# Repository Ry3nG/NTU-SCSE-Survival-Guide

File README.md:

# NTU-SCSE-Survival-Guide
Hi there, I'm glad you found this repository.

I created this repository because one day I was organizing my hard drive and found a lot of code and assignments from my freshman year. I thought it would be a good idea to share it with juniors. I hope this repository will help you in your journey in NTU SCSE. Spread the word and share this repository with your friends.

:sparkles:Please feel free to contribute to this repository and make it better. If you have any questions, feel free to open an issue:sparkles:

:pushpin:Note: This repository is still under construction. I will be adding more content as time goes by. If you have any suggestions, feel free to open an issue.:pushpin:

:no_entry_sign:Disclaimer: I do not guarantee that all the works in this repository is correct. Also, NTU does not endorse this repository. I am not responsible for any consequences that may arise from using this repository. Please remember that no plagiarism is allowed in NTU. Please do not copy and paste the code from this repository. I am not responsible for any consequences that may arise from using this repository. Please use this repository at your own risk. :no_entry_sign:

## What to expect :heavy_plus_sign:

- [x] :books: Study notes
- [x] :page_with_curl: Lab assignments
- [x] :computer: Project assignments 
- [x] :pencil: [Past year exam papers](https://entuedu-my.sharepoint.com/personal/scse-academics_e_ntu_edu_sg/_layouts/15/onedrive.aspx?id=%2Fpersonal%2Fscse%2Dacademics%5Fe%5Fntu%5Fedu%5Fsg%2FDocuments%2FSCSE%20Past%20Year%20Papers&ga=1)

## Directory Structure :file_folder:
* Year 1 Modules
  * [SC1003](https://github.com/Ry3nG/NTU-SCSE-Survival-Guide/blob/63125223ba3fbce1692d6bb430d10afd18555996/Year1/SC1003) - Introduction to Computational Thinking & Programming 
  * [SC1007](https://github.com/Ry3nG/NTU-SCSE-Survival-Guide/blob/63125223ba3fbce1692d6bb430d10afd18555996/Year1/SC1007) - Data Structures & Algorithms 
  * [SC1015](https://github.com/Ry3nG/NTU-SCSE-Survival-Guide/blob/e838eea947de3046945bb1c5bfa82d6b12342de5/Year1/SC1015) - Data Science and Artificial Intelligence
* Year 2 Modules
  * [SC2002](https://github.com/Ry3nG/NTU-SCSE-Survival-Guide/blob/1c191aafbaf08b72edd439501faf1cfb49756c34/Year2/SC2002) - Object Oriented Design & Programming
  * [SC2001](https://github.com/Ry3nG/NTU-SCSE-Survival-Guide/blob/main/Year2/SC2001) - Algorithms Design & Analysis
  * [SC2104](https://github.com/Ry3nG/NTU-SCSE-Survival-Guide/blob/main/Year2/SC2104) - Sensors, Interfacing & Digital Control
  * [SC2107](https://github.com/Ry3nG/NTU-SCSE-Survival-Guide/blob/main/Year2/SC2107) - Microprocessor System Design and Development
  * [SC2103](https://github.com/Ry3nG/NTU-SCSE-Survival-Guide/tree/main/Year2/SC2103) - Digital System Design
  * [SC2005](https://github.com/Ry3nG/NTU-SCSE-Survival-Guide/tree/main/Year2/SC2005) - Operating Systems
  * [SC2008](https://github.com/Ry3nG/NTU-SCSE-Survival-Guide/tree/main/Year2/SC2008) - Computer Networks
* SC2079 - Multi-Disciplinary Design Project
  * I was responsible for the STM and hardware part for the MDP project, the related files can be found [here](https://github.com/Ry3nG/STM32-Robot-Hardware-Control)
* Year 3 Modules
  * [SC3102](https://github.com/Ry3nG/NTU-SCSE-Survival-Guide/tree/year3-mods/Year3/SC3102) - Signals, Systems, and Transforms
  * [SC3103](https://github.com/Ry3nG/NTU-SCSE-Survival-Guide/tree/year3-mods/Year3/SC3103) - Embedded Programming
  * [SC3050](https://github.com/Ry3nG/NTU-SCSE-Survival-Guide/tree/year3-mods/Year3/SC3050) - Advanced Computer Architecture
## What you won't find in this repository :heavy_minus_sign:
Your exam answers, obviously. :sweat_smile:
Also, this repository is not a replacement for your own effort. You should still study hard and do your own research. This repository is providing you with some resources that you can refer to when you struggles.

## Contribute
You have useful information that is missing in here? 
Feel free to contribute to this project and help more future NTU students :sparkles:

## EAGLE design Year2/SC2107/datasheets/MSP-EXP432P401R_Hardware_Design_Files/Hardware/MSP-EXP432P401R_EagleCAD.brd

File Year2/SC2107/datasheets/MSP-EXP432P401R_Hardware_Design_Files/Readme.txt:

MSP-EXP432P401R Hardware Design Files v3.00.00
Texas Instruments, Inc.

********************************************************************************
Welcome to the MSP-EXP432P401R LaunchPad!
********************************************************************************

In this package, you will find hardware design files that can help you quickly
get started on developing your own project.

Available in the 'Hardware' folder are the complete board schematic and layout,
bill of material and Gerber files.

You can also find various web links in the 'Documentation' folder pointing to
the LaunchPad's Homepage, Quick Start Guide, User's Guide, and Software Examples.

For more resources, be sure to visit www.ti.com/tool/msp-exp432p401r

********************************************************************************
Revision History
********************************************************************************
Ver 3.00.00 - June 3rd, 2016
- New Rev2.0 PCB hardware design
- Added BOOSTXL-BATPAKMKII and BOOSTXL-SENSORS demos

Ver 2.10.00 - February 17th, 2016
- Header file, Driver Library updates

Ver 2.00.00 - November 4th, 2015
- Updated demo projects for CMSIS header file updates
- Added CapTouch BoosterPack demos

Ver 1.05.00 - November 4th, 2015
- Bug fixes to demo projects

Ver 1.04.00 - August 24th, 2015
- Fixed Educational Boosterpack MKII example projectSpec include path error in Linux

Ver 1.03.00 - June 22nd, 2015
- Added MacOSX + Linux support for OOB GUI and DSLite
- Added Educational Boosterpack MKII example projects

Ver 1.02.00 - May 15th, 2015
- Added link to Software Examples download

Ver 1.01.02 - April 14th, 2015
- Bug fixes for OutOfBox demo
- Added KEIL project files to software examples
- Updated IAR project files
- Added Blink LED example

Ver 1.00.05 - March 24th, 2015
- Initial Release

********************************************************************************
Project File Listing
********************************************************************************
|--Documentation                      : Folder containing links to more resources
|--Hardware                           : Folder containing hardware design files,
                                        bill of material and gerber files
|--Readme.txt                         : This file

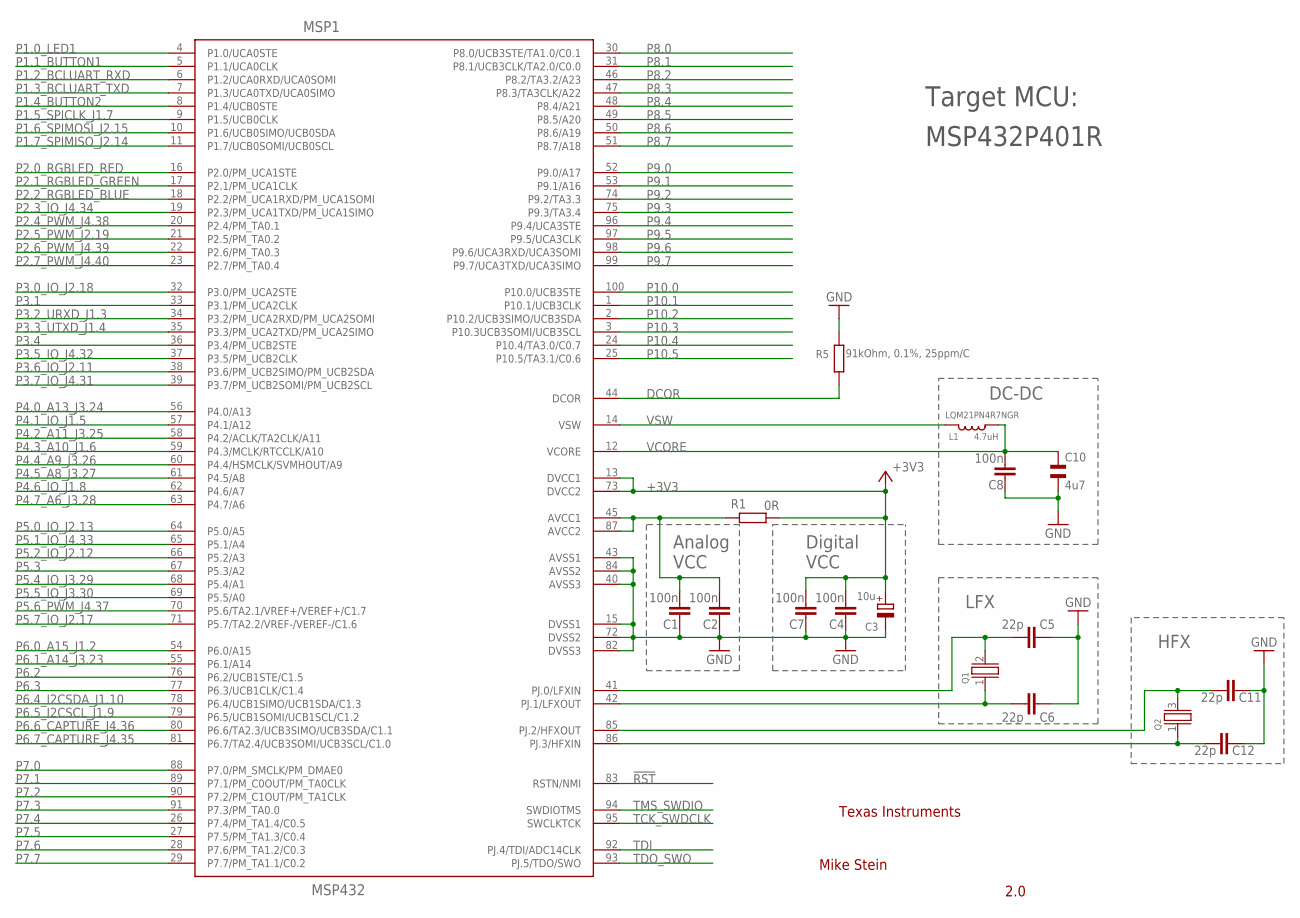
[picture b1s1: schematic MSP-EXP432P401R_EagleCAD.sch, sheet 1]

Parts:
C1, C2, C4, C7, C8: 100n; 0402
C3: 10u; A/3216-18R
C5, C6, C11, C12: 22p; 0402
C10: 4u7; CSMD0805
L1: 4.7uH; 0806
MSP1: MSP432; PZ100
Q1: CRYSTALLF_GENERAL; LF_XTAL
Q2: CRYSTALEPSON_FA-238; FA-238
R1: 0R; 0402
R5: 91kOhm, 0.1%, 25ppm/C; 0805

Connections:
!RST: MSP1.83 (RSTN/NMI); also elsewhere on the board
+3V3: C3.+, C4.1, C7.1, MSP1.13 (DVCC1), MSP1.73 (DVCC2), R1.1; also elsewhere on the board
DCOR: MSP1.44 (DCOR), R5.1
unnamed: C1.1, C2.1, MSP1.45 (AVCC1), MSP1.87 (AVCC2), R1.2
unnamed: C6.1, MSP1.42 (PJ.1/LFXOUT), Q1.1
unnamed: C5.1, MSP1.41 (PJ.0/LFXIN), Q1.2
P1.0_LED1: MSP1.4 (P1.0/UCA0STE); also elsewhere on the board
P1.1_BUTTON1: MSP1.5 (P1.1/UCA0CLK); also elsewhere on the board
P1.2_BCLUART_RXD: MSP1.6 (P1.2/UCA0RXD/UCA0SOMI); also elsewhere on the board
P1.3_BCLUART_TXD: MSP1.7 (P1.3/UCA0TXD/UCA0SIMO); also elsewhere on the board
P1.4_BUTTON2: MSP1.8 (P1.4/UCB0STE); also elsewhere on the board
P1.5_SPICLK_J1.7: MSP1.9 (P1.5/UCB0CLK); also elsewhere on the board
P1.6_SPIMOSI_J2.15: MSP1.10 (P1.6/UCB0SIMO/UCB0SDA); also elsewhere on the board
P1.7_SPIMISO_J2.14: MSP1.11 (P1.7/UCB0SOMI/UCB0SCL); also elsewhere on the board
P2.0_RGBLED_RED: MSP1.16 (P2.0/PM_UCA1STE); also elsewhere on the board
P2.1_RGBLED_GREEN: MSP1.17 (P2.1/PM_UCA1CLK); also elsewhere on the board
P2.2_RGBLED_BLUE: MSP1.18 (P2.2/PM_UCA1RXD/PM_UCA1SOMI); also elsewhere on the board
P2.3_IO_J4.34: MSP1.19 (P2.3/PM_UCA1TXD/PM_UCA1SIMO); also elsewhere on the board
P2.4_PWM_J4.38: MSP1.20 (P2.4/PM_TA0.1); also elsewhere on the board
P2.5_PWM_J2.19: MSP1.21 (P2.5/PM_TA0.2); also elsewhere on the board
P2.6_PWM_J4.39: MSP1.22 (P2.6/PM_TA0.3); also elsewhere on the board
P2.7_PWM_J4.40: MSP1.23 (P2.7/PM_TA0.4); also elsewhere on the board
P3.0_IO_J2.18: MSP1.32 (P3.0/PM_UCA2STE); also elsewhere on the board
P3.1: MSP1.33 (P3.1/PM_UCA2CLK)
P3.2_URXD_J1.3: MSP1.34 (P3.2/PM_UCA2RXD/PM_UCA2SOMI); also elsewhere on the board
P3.3_UTXD_J1.4: MSP1.35 (P3.3/PM_UCA2TXD/PM_UCA2SIMO); also elsewhere on the board
P3.4: MSP1.36 (P3.4/PM_UCB2STE)
P3.5_IO_J4.32: MSP1.37 (P3.5/PM_UCB2CLK); also elsewhere on the board
P3.6_IO_J2.11: MSP1.38 (P3.6/PM_UCB2SIMO/PM_UCB2SDA); also elsewhere on the board
P3.7_IO_J4.31: MSP1.39 (P3.7/PM_UCB2SOMI/PM_UCB2SCL); also elsewhere on the board
P4.0_A13_J3.24: MSP1.56 (P4.0/A13); also elsewhere on the board
P4.1_IO_J1.5: MSP1.57 (P4.1/A12); also elsewhere on the board
P4.2_A11_J3.25: MSP1.58 (P4.2/ACLK/TA2CLK/A11); also elsewhere on the board
P4.3_A10_J1.6: MSP1.59 (P4.3/MCLK/RTCCLK/A10); also elsewhere on the board
P4.4_A9_J3.26: MSP1.60 (P4.4/HSMCLK/SVMHOUT/A9); also elsewhere on the board
P4.5_A8_J3.27: MSP1.61 (P4.5/A8); also elsewhere on the board
P4.6_IO_J1.8: MSP1.62 (P4.6/A7); also elsewhere on the board
P4.7_A6_J3.28: MSP1.63 (P4.7/A6); also elsewhere on the board
P5.0_IO_J2.13: MSP1.64 (P5.0/A5); also elsewhere on the board
P5.1_IO_J4.33: MSP1.65 (P5.1/A4); also elsewhere on the board
P5.2/XT2IN: C12.1, MSP1.86 (PJ.3/HFXIN), Q2.1
P5.2_IO_J2.12: MSP1.66 (P5.2/A3); also elsewhere on the board
P5.3: MSP1.67 (P5.3/A2); also elsewhere on the board
P5.3/XT2OUT: C11.1, MSP1.85 (PJ.2/HFXOUT), Q2.3 (2)
P5.4_IO_J3.29: MSP1.68 (P5.4/A1); also elsewhere on the board
P5.5_IO_J3.30: MSP1.69 (P5.5/A0); also elsewhere on the board
P5.6_PWM_J4.37: MSP1.70 (P5.6/TA2.1/VREF+/VEREF+/C1.7); also elsewhere on the board
P5.7_IO_J2.17: MSP1.71 (P5.7/TA2.2/VREF-/VEREF-/C1.6); also elsewhere on the board
P6.0_A15_J1.2: MSP1.54 (P6.0/A15); also elsewhere on the board
P6.1_A14_J3.23: MSP1.55 (P6.1/A14); also elsewhere on the board
P6.2: MSP1.76 (P6.2/UCB1STE/C1.5); also elsewhere on the board
P6.3: MSP1.77 (P6.3/UCB1CLK/C1.4); also elsewhere on the board
P6.4_I2CSDA_J1.10: MSP1.78 (P6.4/UCB1SIMO/UCB1SDA/C1.3); also elsewhere on the board
P6.5_I2CSCL_J1.9: MSP1.79 (P6.5/UCB1SOMI/UCB1SCL/C1.2); also elsewhere on the board
P6.6_CAPTURE_J4.36: MSP1.80 (P6.6/TA2.3/UCB3SIMO/UCB3SDA/C1.1); also elsewhere on the board
P6.7_CAPTURE_J4.35: MSP1.81 (P6.7/TA2.4/UCB3SOMI/UCB3SCL/C1.0); also elsewhere on the board
P7.0: MSP1.88 (P7.0/PM_SMCLK/PM_DMAE0); also elsewhere on the board
P7.1: MSP1.89 (P7.1/PM_C0OUT/PM_TA0CLK); also elsewhere on the board
P7.2: MSP1.90 (P7.2/PM_C1OUT/PM_TA1CLK); also elsewhere on the board
P7.3: MSP1.91 (P7.3/PM_TA0.0); also elsewhere on the board
P7.4: MSP1.26 (P7.4/PM_TA1.4/C0.5); also elsewhere on the board
P7.5: MSP1.27 (P7.5/PM_TA1.3/C0.4); also elsewhere on the board
P7.6: MSP1.28 (P7.6/PM_TA1.2/C0.3); also elsewhere on the board
P7.7: MSP1.29 (P7.7/PM_TA1.1/C0.2); also elsewhere on the board
P8.0: MSP1.30 (P8.0/UCB3STE/TA1.0/C0.1); also elsewhere on the board
P8.1: MSP1.31 (P8.1/UCB3CLK/TA2.0/C0.0)
P8.2: MSP1.46 (P8.2/TA3.2/A23); also elsewhere on the board
P8.3: MSP1.47 (P8.3/TA3CLK/A22); also elsewhere on the board
P8.4: MSP1.48 (P8.4/A21); also elsewhere on the board
P8.5: MSP1.49 (P8.5/A20); also elsewhere on the board
P8.6: MSP1.50 (P8.6/A19); also elsewhere on the board
P8.7: MSP1.51 (P8.7/A18); also elsewhere on the board
P9.0: MSP1.52 (P9.0/A17); also elsewhere on the board
P9.1: MSP1.53 (P9.1/A16); also elsewhere on the board
P9.2: MSP1.74 (P9.2/TA3.3); also elsewhere on the board
P9.3: MSP1.75 (P9.3/TA3.4); also elsewhere on the board
P9.4: MSP1.96 (P9.4/UCA3STE); also elsewhere on the board
P9.5: MSP1.97 (P9.5/UCA3CLK); also elsewhere on the board
P9.6: MSP1.98 (P9.6/UCA3RXD/UCA3SOMI); also elsewhere on the board
P9.7: MSP1.99 (P9.7/UCA3TXD/UCA3SIMO); also elsewhere on the board
P10.0: MSP1.100 (P10.0/UCB3STE); also elsewhere on the board
P10.1: MSP1.1 (P10.1/UCB3CLK); also elsewhere on the board
P10.2: MSP1.2 (P10.2/UCB3SIMO/UCB3SDA); also elsewhere on the board
P10.3: MSP1.3 (P10.3UCB3SOMI/UCB3SCL); also elsewhere on the board
P10.4: MSP1.24 (P10.4/TA3.0/C0.7); also elsewhere on the board
P10.5: MSP1.25 (P10.5/TA3.1/C0.6); also elsewhere on the board
TCK_SWDCLK: MSP1.95 (SWCLKTCK); also elsewhere on the board
TDI: MSP1.92 (PJ.4/TDI/ADC14CLK); also elsewhere on the board
TDO_SWO: MSP1.93 (PJ.5/TDO/SWO); also elsewhere on the board
TMS_SWDIO: MSP1.94 (SWDIOTMS); also elsewhere on the board
VCORE: C8.1, C10.1, L1.1, MSP1.12 (VCORE)
VSW: L1.2, MSP1.14 (VSW)
XDS-GND: C1.2, C2.2, C3.-, C4.2, C5.2, C6.2, C7.2, C8.2, C10.2, C11.2, C12.2, MSP1.15 (DVSS1), MSP1.40 (AVSS3), MSP1.43 (AVSS1), MSP1.72 (DVSS2), MSP1.82 (DVSS3), MSP1.84 (AVSS2), R5.2; also elsewhere on the board

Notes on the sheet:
Target MCU:
Texas Instruments
LQM21PN4R7NGR
HFX
LFX
Analog
VCC
Digital
DC-DC
MSP432P401R

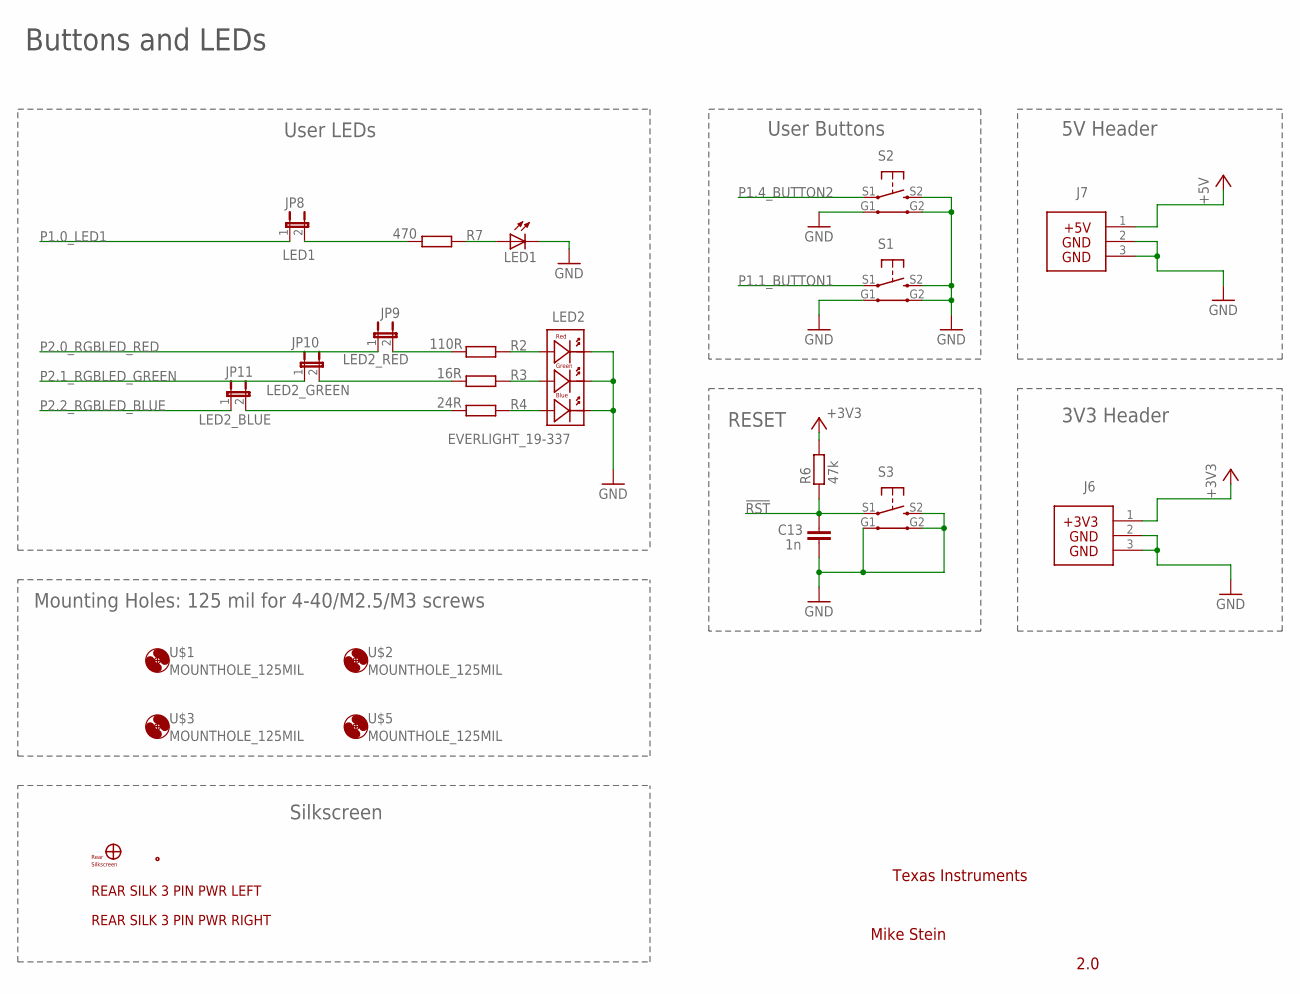
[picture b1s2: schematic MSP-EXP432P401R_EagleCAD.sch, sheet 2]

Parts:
C13: 1n; 0402
J6: HEADER 1X03; 3PIN_PWR_3V3
J7: BP_HEADERS_PWR_5V; 3PIN_PWR_5V
JP8: LED1; JP1M
JP9: LED2_RED; JP1M
JP10: LED2_GREEN; JP1M
JP11: LED2_BLUE; JP1M
LED1: LEDCHIPLED_0603; CHIPLED_0603
LED2: EVERLIGHT_19-337; RGB_LED
R2: 110R; 0402
R3: 16R; 0402
R4: 24R; 0402
R6: 47k; 0402
R7: 470; 0402
S1, S2, S3: TS-1188E
U$1, U$2, U$3, U$5: MOUNTHOLE_125MIL
U$6: SILK_HEADER_LABEL
U$7: MIKE_TM
U$8: P401R_REARSILK_REV2_0
U$9: BP_3PIN_SILK; 3PIN_PWR_SILK
U$10: BP_3PIN_SILK_RT; 3PIN_PWR_SILK_RT

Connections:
!RST: C13.1, R6.1, S3.S1; also elsewhere on the board
+3V3: J6.1, R6.2; also elsewhere on the board
+5V: J7.1; also elsewhere on the board
unnamed: JP9.2, R2.1
unnamed: LED2.5 (RA), R2.2
unnamed: LED2.6 (GA), R3.2
unnamed: LED2.4 (BA), R4.2
unnamed: LED1.A, R7.2
unnamed: JP10.2, R3.1
unnamed: JP11.2, R4.1
unnamed: JP8.2, R7.1
P1.0_LED1: JP8.1; also elsewhere on the board
P1.1_BUTTON1: S1.S1; also elsewhere on the board
P1.4_BUTTON2: S2.S1; also elsewhere on the board
P2.0_RGBLED_RED: JP9.1; also elsewhere on the board
P2.1_RGBLED_GREEN: JP10.1; also elsewhere on the board
P2.2_RGBLED_BLUE: JP11.1; also elsewhere on the board
XDS-GND: C13.2, J6.2, J6.3, J7.2, J7.3, LED1.C, LED2.1 (BC), LED2.2 (RC), LED2.3 (GC), S1.G1, S1.G2, S1.S2 (S), S2.G1, S2.G2, S2.S2 (S), S3.G1, S3.G2, S3.S2 (S); also elsewhere on the board

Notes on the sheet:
User LEDs
User Buttons
RESET
Buttons and LEDs
5V Header
3V3 Header
Mounting Holes: 125 mil for 4-40/M2.5/M3 screws
Silkscreen
Texas Instruments

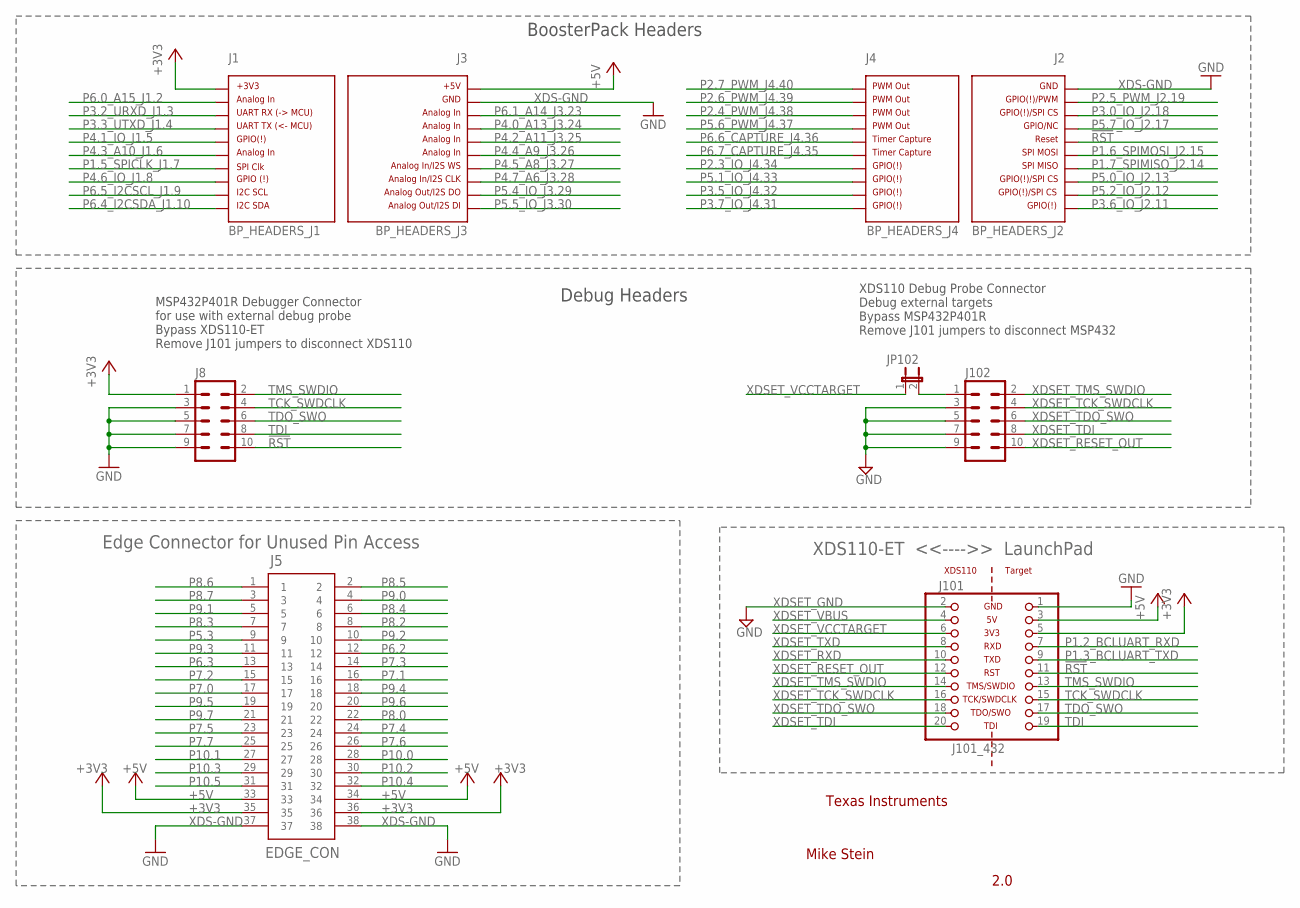
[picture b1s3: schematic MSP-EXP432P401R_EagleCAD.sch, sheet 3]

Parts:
J1: BP_HEADERS_J1; J1
J2: BP_HEADERS_J2; J2
J3: BP_HEADERS_J3; J3
J4: BP_HEADERS_J4; J4
J5: EDGE_CON; BOTTOM_CONNECTOR
J8, J102: DEBUG_ARM-10; ARM-10
J101: J101_432
JP102: JP1M

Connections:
!RST: J2.16, J8.10, J101.11; also elsewhere on the board
+3V3: J1.1, J5.35, J5.36, J8.1, J101.5; also elsewhere on the board
+5V: J3.21, J5.33, J5.34, J101.3; also elsewhere on the board
unnamed: J102.1, JP102.2
P1.2_BCLUART_RXD: J101.7; also elsewhere on the board
P1.3_BCLUART_TXD: J101.9; also elsewhere on the board
P1.5_SPICLK_J1.7: J1.7; also elsewhere on the board
P1.6_SPIMOSI_J2.15: J2.15; also elsewhere on the board
P1.7_SPIMISO_J2.14: J2.14; also elsewhere on the board
P2.3_IO_J4.34: J4.34; also elsewhere on the board
P2.4_PWM_J4.38: J4.38; also elsewhere on the board
P2.5_PWM_J2.19: J2.19; also elsewhere on the board
P2.6_PWM_J4.39: J4.39; also elsewhere on the board
P2.7_PWM_J4.40: J4.40; also elsewhere on the board
P3.0_IO_J2.18: J2.18; also elsewhere on the board
P3.2_URXD_J1.3: J1.3; also elsewhere on the board
P3.3_UTXD_J1.4: J1.4; also elsewhere on the board
P3.5_IO_J4.32: J4.32; also elsewhere on the board
P3.6_IO_J2.11: J2.11; also elsewhere on the board
P3.7_IO_J4.31: J4.31; also elsewhere on the board
P4.0_A13_J3.24: J3.24; also elsewhere on the board
P4.1_IO_J1.5: J1.5; also elsewhere on the board
P4.2_A11_J3.25: J3.25; also elsewhere on the board
P4.3_A10_J1.6: J1.6; also elsewhere on the board
P4.4_A9_J3.26: J3.26; also elsewhere on the board
P4.5_A8_J3.27: J3.27; also elsewhere on the board
P4.6_IO_J1.8: J1.8; also elsewhere on the board
P4.7_A6_J3.28: J3.28; also elsewhere on the board
P5.0_IO_J2.13: J2.13; also elsewhere on the board
P5.1_IO_J4.33: J4.33; also elsewhere on the board
P5.2_IO_J2.12: J2.12; also elsewhere on the board
P5.3: J5.9; also elsewhere on the board
P5.4_IO_J3.29: J3.29; also elsewhere on the board
P5.5_IO_J3.30: J3.30; also elsewhere on the board
P5.6_PWM_J4.37: J4.37; also elsewhere on the board
P5.7_IO_J2.17: J2.17; also elsewhere on the board
P6.0_A15_J1.2: J1.2; also elsewhere on the board
P6.1_A14_J3.23: J3.23; also elsewhere on the board
P6.2: J5.12; also elsewhere on the board
P6.3: J5.13; also elsewhere on the board
P6.4_I2CSDA_J1.10: J1.10; also elsewhere on the board
P6.5_I2CSCL_J1.9: J1.9; also elsewhere on the board
P6.6_CAPTURE_J4.36: J4.36; also elsewhere on the board
P6.7_CAPTURE_J4.35: J4.35; also elsewhere on the board
P7.0: J5.17; also elsewhere on the board
P7.1: J5.16; also elsewhere on the board
P7.2: J5.15; also elsewhere on the board
P7.3: J5.14; also elsewhere on the board
P7.4: J5.24; also elsewhere on the board
P7.5: J5.23; also elsewhere on the board
P7.6: J5.26; also elsewhere on the board
P7.7: J5.25; also elsewhere on the board
P8.0: J5.22; also elsewhere on the board
P8.2: J5.8; also elsewhere on the board
P8.3: J5.7; also elsewhere on the board
P8.4: J5.6; also elsewhere on the board
P8.5: J5.2; also elsewhere on the board
P8.6: J5.1; also elsewhere on the board
P8.7: J5.3; also elsewhere on the board
P9.0: J5.4; also elsewhere on the board
P9.1: J5.5; also elsewhere on the board
P9.2: J5.10; also elsewhere on the board
P9.3: J5.11; also elsewhere on the board
P9.4: J5.18; also elsewhere on the board
P9.5: J5.19; also elsewhere on the board
P9.6: J5.20; also elsewhere on the board
P9.7: J5.21; also elsewhere on the board
P10.0: J5.28; also elsewhere on the board
P10.1: J5.27; also elsewhere on the board
P10.2: J5.30; also elsewhere on the board
P10.3: J5.29; also elsewhere on the board
P10.4: J5.32; also elsewhere on the board
P10.5: J5.31; also elsewhere on the board
TCK_SWDCLK: J8.4, J101.15; also elsewhere on the board
TDI: J8.8, J101.19; also elsewhere on the board
TDO_SWO: J8.6, J101.17; also elsewhere on the board
TMS_SWDIO: J8.2, J101.13; also elsewhere on the board
XDS-GND: J2.20, J3.22, J5.37, J5.38, J8.3, J8.5, J8.7, J8.9, J101.1; also elsewhere on the board
XDSET_GND: J101.2, J102.3, J102.5, J102.7, J102.9; also elsewhere on the board
XDSET_RESET_OUT: J101.12, J102.10; also elsewhere on the board
XDSET_RXD: J101.10; also elsewhere on the board
XDSET_TCK_SWDCLK: J101.16, J102.4; also elsewhere on the board
XDSET_TDI: J101.20, J102.8; also elsewhere on the board
XDSET_TDO_SWO: J101.18, J102.6; also elsewhere on the board
XDSET_TMS_SWDIO: J101.14, J102.2; also elsewhere on the board
XDSET_TXD: J101.8; also elsewhere on the board
XDSET_VBUS: J101.4; also elsewhere on the board
XDSET_VCCTARGET: J101.6, JP102.1; also elsewhere on the board

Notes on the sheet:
BoosterPack Headers
XDS110-ET <<---->> LaunchPad
Edge Connector for Unused Pin Access
Texas Instruments
MSP432P401R Debugger Connector for use with external debug probe Bypass XDS110-ET Remove J101 jumpers to disconnect XDS110
XDS110 Debug Probe Connector Debug external targets Bypass MSP432P401R Remove J101 jumpers to disconnect MSP432
Debug Headers

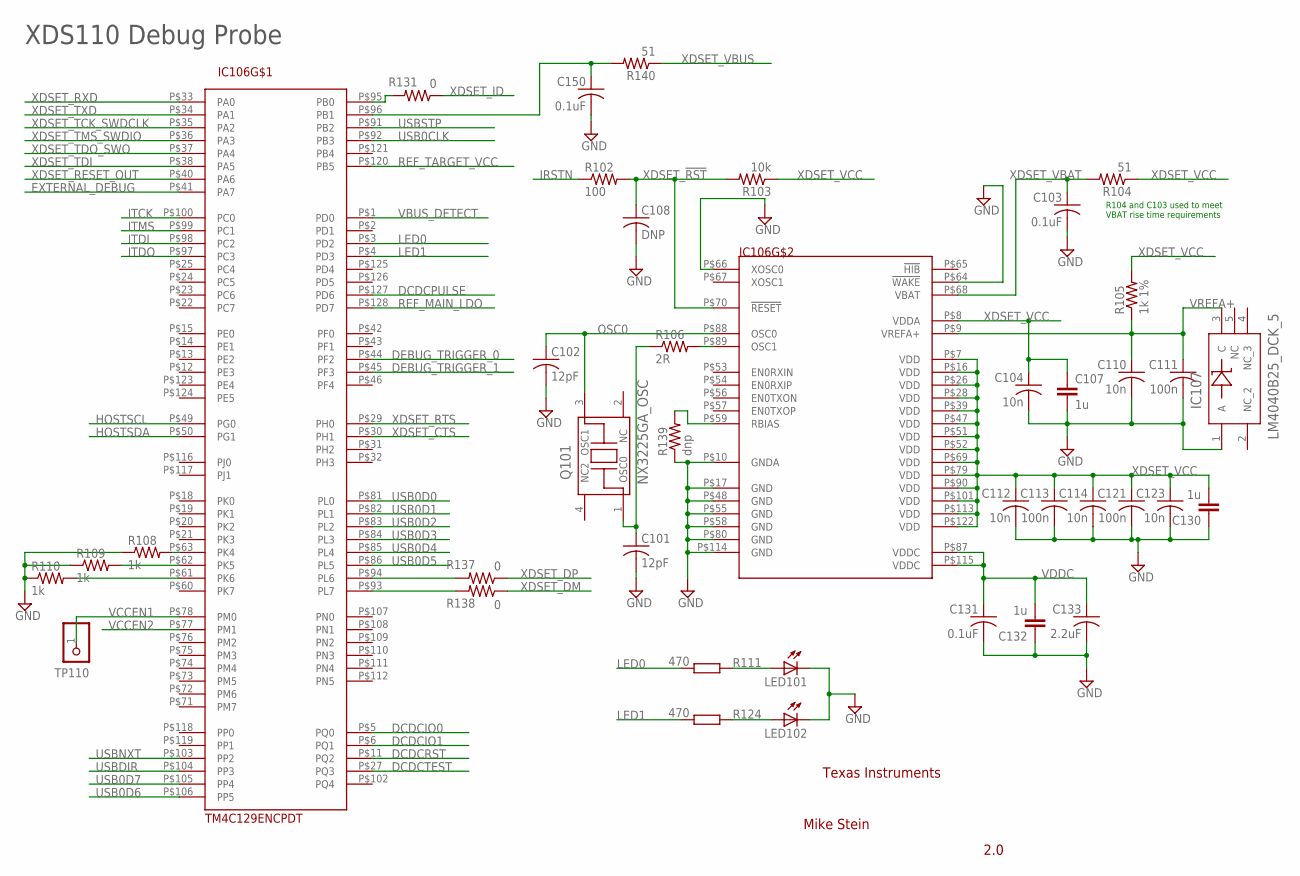
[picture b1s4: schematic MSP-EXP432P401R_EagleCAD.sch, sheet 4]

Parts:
C101, C102: 12pF; C0402
C103, C131, C150: 0.1uF; C0402
C104, C110, C112, C114, C123: 10n; C0402
C107, C130, C132: 1u; C0603
C108: DNP; C0402
C111, C113, C121: 100n; C0402
C133: 2.2uF; C0603K; DIGIKEY_PARTNUM 311-1451-2-ND
IC106: TM4C129ENCPDT; TQFP-128
IC107: LM4040B25_DCK_5; DCK5
LED101, LED102: LEDCHIPLED_0603; CHIPLED_0603
Q101: NX3225GA_OSC; NX3225GA
R102: 100; R0402
R103: 10k; R0402
R104, R140: 51; R0402
R105: 1k 1%; R0402
R106: 2R; R0402
R108, R109, R110: 1k; R0402
R111, R124: 470; 0402
R131, R137, R138: 0; R0402
R139: dnp; R0402
TP110: TEST_PIN2; 1X01

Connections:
DCDCIO0: IC106.P$5 (PQ0); also elsewhere on the board
DCDCIO1: IC106.P$6 (PQ1); also elsewhere on the board
DCDCPULSE: IC106.P$127 (PD6); also elsewhere on the board
DCDCRST: IC106.P$11 (PQ2); also elsewhere on the board
DCDCTEST: IC106.P$27 (PQ3); also elsewhere on the board
DEBUG_TRIGGER_0: IC106.P$44 (PF2)
DEBUG_TRIGGER_1: IC106.P$45 (PF3)
EXTERNAL_DEBUG: IC106.P$41 (PA7)
HOSTSCL: IC106.P$49 (PG0); also elsewhere on the board
HOSTSDA: IC106.P$50 (PG1); also elsewhere on the board
IRSTN: R102.1; also elsewhere on the board
ITCK: IC106.P$100 (PC0); also elsewhere on the board
ITDI: IC106.P$98 (PC2); also elsewhere on the board
ITDO: IC106.P$97 (PC3); also elsewhere on the board
ITMS: IC106.P$99 (PC1); also elsewhere on the board
LED0: IC106.P$3 (PD2), R111.1
LED1: IC106.P$4 (PD3), R124.1
unnamed: IC106.P$63 (PK4), R108.2
unnamed: LED102.A, R124.2
unnamed: LED101.A, R111.2
unnamed: IC106.P$93 (PL7), R138.2
unnamed: IC106.P$61 (PK6), R110.2
unnamed: IC106.P$95 (PB0), R131.2
unnamed: IC106.P$62 (PK5), R109.2
unnamed: IC106.P$59 (RBIAS), R139.2
OSC0: C102.1, IC106.P$88 (OSC0), Q101.3 (OSC1)
OSC1: IC106.P$89 (OSC1), R106.2
OSC1_R: C101.1, Q101.1 (OSC0), R106.1
P96VBUS: C150.1, IC106.P$96 (PB1), R140.2
REF_MAIN_LDO: IC106.P$128 (PD7); also elsewhere on the board
REF_TARGET_VCC: IC106.P$120 (PB5); also elsewhere on the board
USB0CLK: IC106.P$92 (PB3)
USB0D0: IC106.P$81 (PL0)
USB0D1: IC106.P$82 (PL1)
USB0D2: IC106.P$83 (PL2)
USB0D3: IC106.P$84 (PL3)
USB0D4: IC106.P$85 (PL4)
USB0D5: IC106.P$86 (PL5)
USB0D6: IC106.P$106 (PP5)
USB0D7: IC106.P$105 (PP4)
USBDIR: IC106.P$104 (PP3)
USBNXT: IC106.P$103 (PP2)
USBSTP: IC106.P$91 (PB2)
VBUS_DETECT: IC106.P$1 (PD0); also elsewhere on the board
VCCEN1: IC106.P$78 (PM0), TP110.1; also elsewhere on the board
VCCEN2: IC106.P$77 (PM1)
VDDC: C131.1, C132.2, C133.1, IC106.P$87 (VDDC), IC106.P$115 (VDDC)
VREFA+: C110.1, C111.1, IC106.P$9 (VREFA+), IC107.3 (C), R105.1
XDSET_!RST: C108.1, IC106.P$70 (!RESET), R102.2, R103.2
XDSET_CTS: IC106.P$30 (PH1)
XDSET_DM: R138.1; also elsewhere on the board
XDSET_DP: R137.1; also elsewhere on the board
XDSET_DPR: IC106.P$94 (PL6), R137.2
XDSET_GND: C101.2, C102.2, C103.2, C104.2, C107.2, C108.2, C110.2, C111.2, C112.2, C113.2, C114.2, C121.2, C123.2, C130.1, C131.2, C132.1, C133.2, C150.2, IC106.P$10 (GNDA), IC106.P$17 (GND), IC106.P$48 (GND), IC106.P$55 (GND), IC106.P$58 (GND), IC106.P$64 (!WAKE), IC106.P$66 (XOSC0), IC106.P$80 (GND), IC106.P$114 (GND), IC107.1 (A), LED101.C, LED102.C, R108.1, R109.1, R110.1, R139.1; also elsewhere on the board
XDSET_ID: R131.1; also elsewhere on the board
XDSET_RESET_OUT: IC106.P$40 (PA6); also elsewhere on the board
XDSET_RTS: IC106.P$29 (PH0)
XDSET_RXD: IC106.P$33 (PA0); also elsewhere on the board
XDSET_TCK_SWDCLK: IC106.P$35 (PA2); also elsewhere on the board
XDSET_TDI: IC106.P$38 (PA5); also elsewhere on the board
XDSET_TDO_SWO: IC106.P$37 (PA4); also elsewhere on the board
XDSET_TMS_SWDIO: IC106.P$36 (PA3); also elsewhere on the board
XDSET_TXD: IC106.P$34 (PA1); also elsewhere on the board
XDSET_VBAT: C103.1, IC106.P$68 (VBAT), R104.2
XDSET_VBUS: R140.1; also elsewhere on the board
XDSET_VCC: C104.1, C107.1, C112.1, C113.1, C114.1, C121.1, C123.1, C130.2, IC106.P$7 (VDD), IC106.P$8 (VDDA), IC106.P$16 (VDD), IC106.P$26 (VDD), IC106.P$28 (VDD), IC106.P$39 (VDD), IC106.P$47 (VDD), IC106.P$51 (VDD), IC106.P$52 (VDD), IC106.P$69 (VDD), IC106.P$79 (VDD), IC106.P$90 (VDD), IC106.P$101 (VDD), IC106.P$113 (VDD), IC106.P$122 (VDD), R103.1, R104.1, R105.2; also elsewhere on the board

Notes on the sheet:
R104 and C103 used to meet VBAT rise time requirements
XDS110 Debug Probe
Texas Instruments

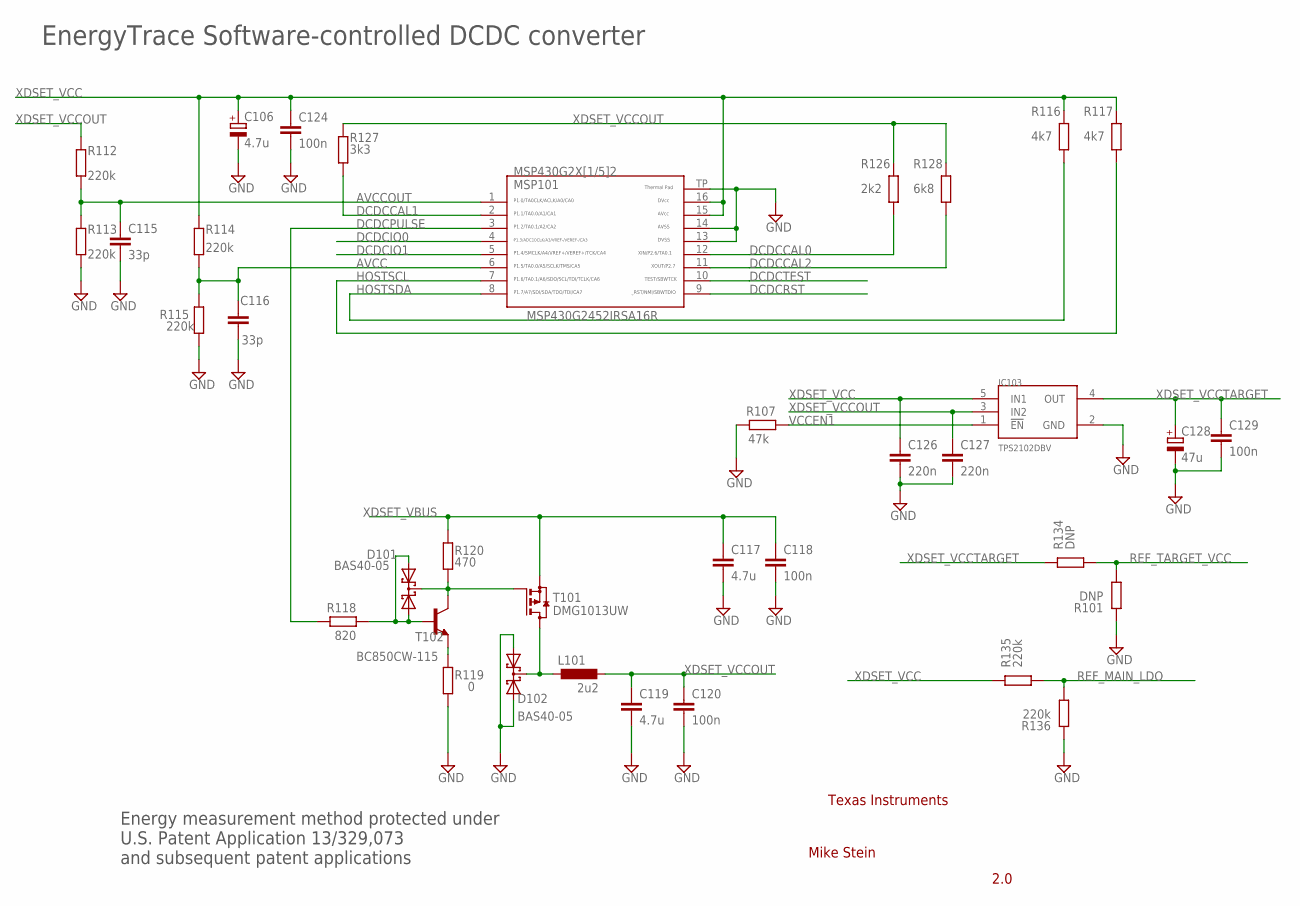
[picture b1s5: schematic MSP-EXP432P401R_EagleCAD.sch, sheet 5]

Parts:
C106: 4.7u; A/3216-18R
C115, C116: 33p; 0402
C117, C119: 4.7u; C0603
C118, C120, C124, C129: 100n; 0402
C126, C127: 220n; 0402
C128: 47u; A/3216-18R
D101, D102: BAS40-05; SOT23
IC103: TPS2102DBV; SOT23-5
L101: 2u2; L3216C
MSP101: MSP430G2452IRSA16R; RSA16
R101, R134: DNP; 0402
R107: 47k; 0402
R112, R113, R114, R115, R135, R136: 220k; 0402
R116, R117: 4k7; 0402
R118: 820; 0402
R119: 0; 0402
R120: 470; 0402
R126: 2k2; 0402
R127: 3k3; 0402
R128: 6k8; 0402
T101: DMG1013UW; SOT23
T102: BC850CW-115; SOT23-BEC

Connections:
AVCC: C116.2, MSP101.6, R114.2, R115.1
AVCCOUT: C115.2, MSP101.1, R112.2, R113.1
DCDCCAL0: MSP101.12, R126.2
DCDCCAL1: MSP101.2, R127.2
DCDCCAL2: MSP101.11, R128.2
DCDCIO0: MSP101.4; also elsewhere on the board
DCDCIO1: MSP101.5; also elsewhere on the board
DCDCPULSE: MSP101.3, R118.2; also elsewhere on the board
DCDCRST: MSP101.9; also elsewhere on the board
DCDCTEST: MSP101.10; also elsewhere on the board
HOSTSCL: MSP101.7, R117.2; also elsewhere on the board
HOSTSDA: MSP101.8, R116.2; also elsewhere on the board
unnamed: R119.1, T102.E
unnamed: D101.1 (A1), D101.2 (A2), R118.1, T102.B
unnamed: D102.3 (C), L101.1, T101.3 (D)
unnamed: D101.3 (C), R120.2, T101.1 (G), T102.C
REF_MAIN_LDO: R135.2, R136.2; also elsewhere on the board
REF_TARGET_VCC: R101.2, R134.2; also elsewhere on the board
VCCEN1: IC103.1 (!EN), R107.1; also elsewhere on the board
XDSET_GND: C106.-, C115.1, C116.1, C117.2, C118.2, C119.2, C120.2, C124.2, C126.2, C127.2, C128.-, C129.2, D102.1 (A1), D102.2 (A2), IC103.2 (GND), MSP101.13, MSP101.14, MSP101.TP, R101.1, R107.2, R113.2, R115.2, R119.2, R136.1; also elsewhere on the board
XDSET_VBUS: C117.1, C118.1, R120.1, T101.2 (S); also elsewhere on the board
XDSET_VCC: C106.+, C124.1, C126.1, IC103.5 (IN1), MSP101.15, MSP101.16, R114.1, R116.1, R117.1, R135.1; also elsewhere on the board
XDSET_VCCOUT: C119.1, C120.1, C127.1, IC103.3 (IN2), L101.2, R112.1, R126.1, R127.1, R128.1
XDSET_VCCTARGET: C128.+, C129.1, IC103.4 (OUT), R134.1; also elsewhere on the board

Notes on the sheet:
EnergyTrace Software-controlled DCDC converter
MSP430G2452IRSA16R
Energy measurement method protected under U.S. Patent Application 13/329,073 and subsequent patent applications
Texas Instruments

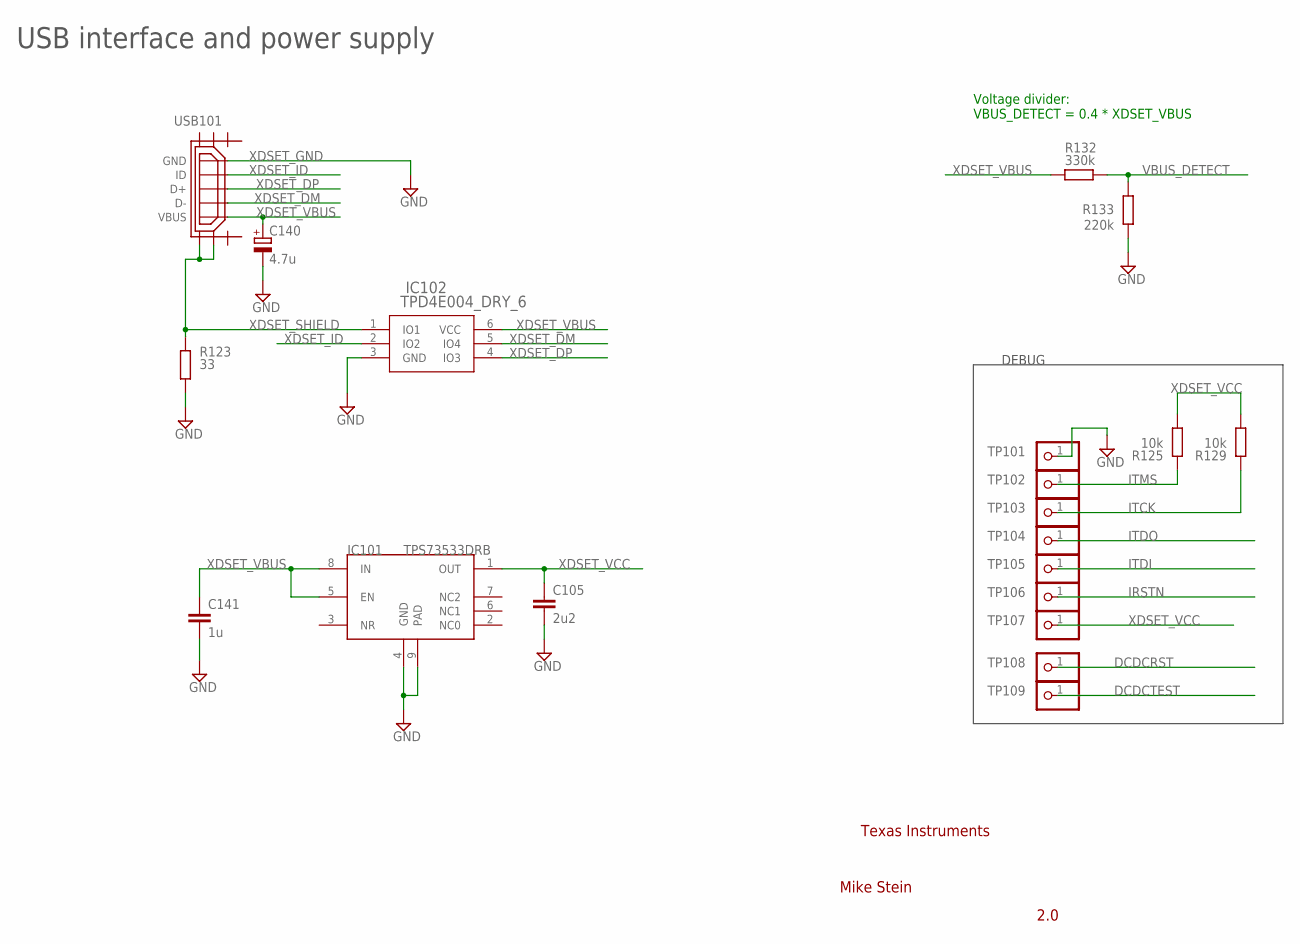
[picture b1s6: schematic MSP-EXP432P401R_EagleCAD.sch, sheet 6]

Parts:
C105: 2u2; C0603
C140: 4.7u; A/3216-18R
C141: 1u; C0603
IC101: TPS73533DRB; SON8
IC102: TPD4E004_DRY_6; DRY6
R123: 33; 0402
R125, R129: 10k; 0402
R132: 330k; 0402
R133: 220k; 0402
TP101, TP102, TP103, TP104, TP105, TP106, TP107, TP108, TP109: TEST_PIN2; 1X01
USB101: USB-MICRO; MOLEX_105164-0001

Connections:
DCDCRST: TP108.1; also elsewhere on the board
DCDCTEST: TP109.1; also elsewhere on the board
IRSTN: TP106.1; also elsewhere on the board
ITCK: R129.1, TP103.1; also elsewhere on the board
ITDI: TP105.1; also elsewhere on the board
ITDO: TP104.1; also elsewhere on the board
ITMS: R125.1, TP102.1; also elsewhere on the board
VBUS_DETECT: R132.2, R133.2; also elsewhere on the board
XDSET_DM: IC102.5 (IO4), USB101.D-; also elsewhere on the board
XDSET_DP: IC102.4 (IO3), USB101.D+; also elsewhere on the board
XDSET_GND: C105.2, C140.-, C141.2, IC101.4 (GND), IC101.9 (PAD), IC102.3 (GND), R123.2, R133.1, TP101.1, USB101.GND; also elsewhere on the board
XDSET_ID: IC102.2 (IO2), USB101.ID; also elsewhere on the board
XDSET_SHIELD: IC102.1 (IO1), R123.1, USB101.SHIELD_TH1 (SHIELD5), USB101.SHIELD_TH2 (SHIELD6)
XDSET_VBUS: C140.+, C141.1, IC101.5 (EN), IC101.8 (IN), IC102.6 (VCC), R132.1, USB101.VBUS; also elsewhere on the board
XDSET_VCC: C105.1, IC101.1 (OUT), R125.2, R129.2, TP107.1; also elsewhere on the board

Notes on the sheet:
USB interface and power supply
DEBUG
Voltage divider: VBUS_DETECT = 0.4 * XDSET_VBUS
Texas Instruments

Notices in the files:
Year2/SC2107/datasheets/MSP-EXP432P401R_Hardware_Design_Files/Hardware/MSP-EXP432P401R_EagleCAD.brd:
(C)2003 A. DANNENBERG
parts and their libraries:
TI-LaunchPad-Eagle: As far as I know the LaunchPad rocket is released by TI under the Creative Commons license.
